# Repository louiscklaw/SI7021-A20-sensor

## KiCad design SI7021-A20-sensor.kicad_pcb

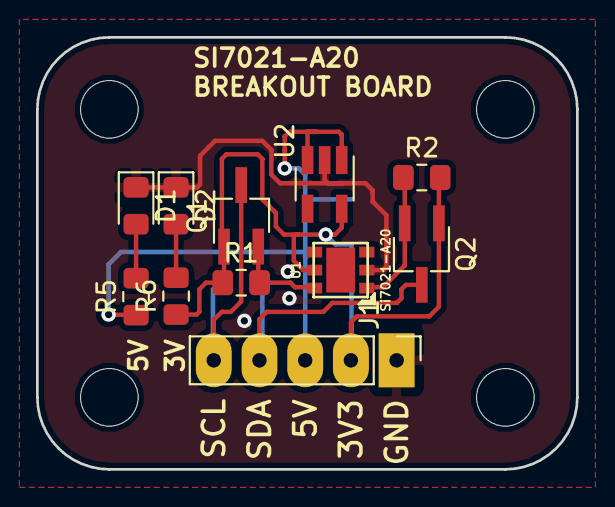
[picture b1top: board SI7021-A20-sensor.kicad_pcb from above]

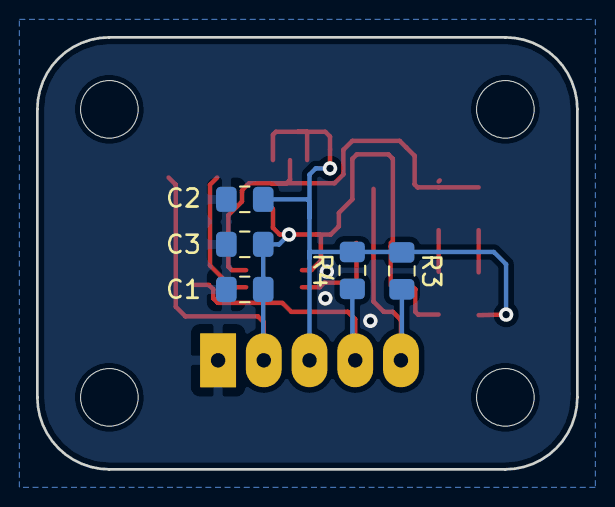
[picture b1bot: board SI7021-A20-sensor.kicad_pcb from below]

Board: 2 copper layers, 30.0 x 24.0 mm, 16 parts (5 on the bottom side), 9 nets.

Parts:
C1: 104; C_0805_2012Metric_Pad1.15x1.40mm_HandSolder
C2, C3: 106; C_0805_2012Metric_Pad1.15x1.40mm_HandSolder
D1, D2: LED; LED_0805_2012Metric_Pad1.15x1.40mm_HandSolder
J1: Conn_01x05; Pin_Header_Straight_1x05_Pitch2.54mm
Q1, Q2: BSS138; TSOT-23_HandSoldering
R1, R2, R3, R4: 103; R_0805_2012Metric_Pad1.15x1.40mm_HandSolder
R5: 102; R_0805_2012Metric_Pad1.15x1.40mm_HandSolder
R6: 501; R_0805_2012Metric_Pad1.15x1.40mm_HandSolder
U1: Si7021-A20; dfn6-3x3
U2: MIC5225-3.3; SOT-23-5_HandSoldering

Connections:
+3V3: C1.1, C3.1, J1.2, Q1.1, Q2.1, R1.1, R2.2, R6.1, U1.5, U2.5
+5V: C2.1, J1.3, R3.1, R4.2, R5.1, U2.1, U2.3
/SCL: J1.5, Q1.3, R3.2
/SCL_3V3: Q1.2, R1.2, U1.6
/SDA: J1.4, Q2.3, R4.1
/SDA_3V3: Q2.2, R2.1, U1.1
GND: C1.2, C2.2, C3.2, D1.1, D2.1, J1.1, U1.2, U2.2
unnamed: D1.2, R5.2
unnamed: D2.2, R6.2

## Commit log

2018-10-06 init commit,
2018-10-11 update,
